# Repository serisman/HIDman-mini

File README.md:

# HIDman-mini
A USB keyboard/mouse to PS/2 (or AT, Serial) computer adapter.

Based on and compatible with: [HIDman](https://github.com/rasteri/HIDman) by [rasteri](https://github.com/rasteri)
 - In the Makefile, make sure the correct `BOARD_TYPE` is selected and then make sure `OSC_TYPE = OSC_INTERNAL` is enabled and `OSC_TYPE = OSC_EXTERNAL` is disabled.  Re-compile and flash the firmware following the instructions found in the HIDman firmware.
   - For HIDman-mini: Choose `BOARD_TYPE = BOARD_AXP` (for ps/2 and serial support), or `BOARD_TYPE = BOARD_MINI` (for just ps/2 support).
   - For HIDman-micro: Choose `BOARD_TYPE = BOARD_MICRO` (only has ps/2 support).
     - Optionally switch to `BOARD_OPTIONS = OPT_SWAP_KBD_MSC` to make it a bit easier to wire up a combo ps/2 port.

### PCBs
- [HIDman-mini](KiCad%20PCBs/HIDman-mini/)
- [HIDman-micro](KiCad%20PCBs/HIDman-micro/)
- [DB9-to-TTL](KiCad%20PCBs/DB9-to-TTL/)

### 3D Printer Models
- [Cover for HIDman-mini](3D%20Printer%20Models/HIDman-mini/)
- [Shell for DB9-to-TTL](3D%20Printer%20Models/DB9-Shell/)

### Schematics
(for HIDman-mini)

(for DB9-to-TTL)

NOTE: Remember to cross-over TxD <--> RxD, and RTS <--> CTS when connecting the two PCBs!

### Optional Configuration: Combo PS/2 Keyboard/Mouse Connector
(for computers that support it)

### Copyright and License:
- Copyright (C) 2022 - serisman (github@serisman.com)
- License: [GPL v3 (or later)](LICENSE)

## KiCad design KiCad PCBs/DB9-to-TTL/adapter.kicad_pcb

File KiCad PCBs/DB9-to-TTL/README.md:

[Home](/README.md)
# PCB: DB9-to-TTL

Order from [OSHPARK](https://oshpark.com/shared_projects/djSCnWyn) or upload [gerber.zip](output/gerber.zip) to your favorite PCB board fabricator.

### Notes:
- Remember to cross-over TxD <--> RxD, and RTS <--> CTS when connecting to the main PCB!
- The older MAX232 can be used in place of the MAX3232.  Might need to change the capacitor values.

### Schematic
- Capacitors are 0603

### Soldered PCB

### Raw PCB

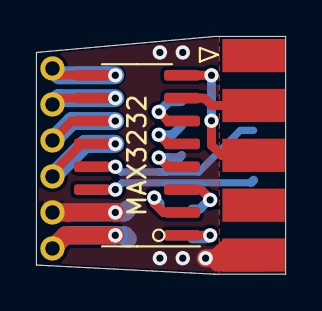
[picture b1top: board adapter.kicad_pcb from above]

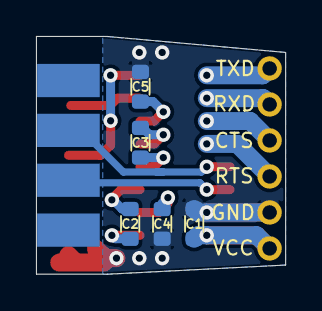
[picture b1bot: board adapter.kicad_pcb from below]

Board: 2 copper layers, 13.8 x 13.2 mm, 8 parts (6 on the bottom side), 16 nets.

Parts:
C1, C2: 100n; C_0603
C3, C4, C5: 1u; C_0603
J1: Conn_01x06; PinHeader_1x06_P2.00mm_Vertical
P1: DB9_Female; DSUB-9_Female_EdgeMount_P2.77mm
U1: MAX3232; SOP-16_3.9x9.9mm_P1.27mm

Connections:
/CTS_232: P1.8, U1.14
/RTS_232: P1.7, U1.13
/RXD_232: P1.2, U1.7
/TXD_232: P1.3, U1.8
CTS: J1.3, U1.11
GND: C1.2, C4.1, C5.1, J1.5, P1.5, U1.15
unnamed: C2.1, U1.1
unnamed: C2.2, U1.3
unnamed: C3.1, U1.4
unnamed: C3.2, U1.5
unnamed: C4.2, U1.2
unnamed: C5.2, U1.6
RTS: J1.4, U1.12
RXD: J1.2, U1.10
TXD: J1.1, U1.9
VCC: C1.1, J1.6, U1.16

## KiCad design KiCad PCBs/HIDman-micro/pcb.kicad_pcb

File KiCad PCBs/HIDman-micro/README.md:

[Home](/README.md)
# PCB: HIDman-micro

Order from [OSHPARK](https://oshpark.com/shared_projects/RKMXx0oz) or upload [gerber.zip](output/gerber.zip) to your favorite PCB board fabricator.

### Notes:
- **WARNING!** Make sure you install the USB port in the correct orientation!
- **WARNING!** Double and Triple check your PS/2 cable pinout to make sure you don't feed 5V where it shouldn't go!

### Firmware

Compatible with HIDman firmware: https://github.com/rasteri/HIDman

```
make clean
make BOARD_TYPE=HIDMAN_MICRO OSC_TYPE=OSC_INTERNAL flash
... or (if you want to swap Keyboard-Data with Mouse-Clock for easier soldering of combo PS/2 port) ...
make clean
make BOARD_TYPE=HIDMAN_MICRO BOARD_OPTIONS=OPT_SWAP_KBD_MSC OSC_TYPE=OSC_INTERNAL flash
```

### Schematic
- USB port P1 (on bottom side) is required for loading code, and can be used for USB keyboard/mouse (including keyboard/mouse combo wireless adapters).
- Hold down SW1 while plugging USB port into computer to force bootloader.
- Resistors are 0603
- Capacitors are 0603 (100n and 3u3) and 0805 (10u)

**WARNING!** This uses a different pinout than HIDman-mini.  Runtime detection can read P4.7, check if it is LOW or floating, and adjust the PS/2 pins accordingly.

### Soldered PCB

### 3D Render

### Raw PCB

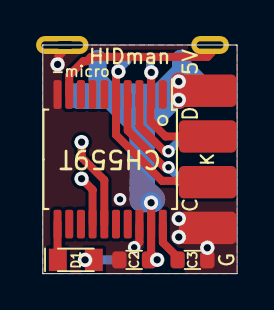
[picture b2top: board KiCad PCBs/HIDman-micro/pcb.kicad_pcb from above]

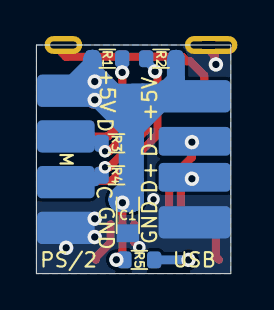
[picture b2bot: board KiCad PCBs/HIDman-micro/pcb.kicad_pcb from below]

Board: 2 copper layers, 10.8 x 12.7 mm, 13 parts (6 on the bottom side), 12 nets.

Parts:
C1: 10u; C_0805
C2: 100n; C_0603
C3: 3u3; C_0603
D1: LED; LED_0805
J1: Conn_02x04_Odd_Even; PinHeader_2x04_P2.54mm_Edge
P1: USB_A; USB_A_Female_SMD_Edge
R1, R2, R3, R4: 2k2; R_0603
R5: 1k; R_0603
SW1: SW_Push; SW_SPST_Edge
U1: CH559T; SSOP-20_5.3x7.2mm_P0.65mm

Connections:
+3V3: C3.1, U1.20
+5V: C1.1, C2.1, J1.1, J1.2, P1.1, R1.1, R2.1, R3.1, R4.1, R5.1, U1.19
GND: C1.2, C2.2, C3.2, J1.7, J1.8, P1.4, SW1.1, U1.10, U1.18
KB_CLK: J1.5, R2.2, U1.5
KB_DATA: J1.3, R1.2, U1.2
MS_CLK: J1.6, R4.2, U1.4
MS_DATA: J1.4, R3.2, U1.3
unnamed: D1.1, U1.11
unnamed: D1.2, R5.2
unnamed: SW1.2, U1.9
USB_D+: P1.3, U1.14
USB_D-: P1.2, U1.15

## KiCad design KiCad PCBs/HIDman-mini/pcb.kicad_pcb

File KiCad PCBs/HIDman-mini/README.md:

[Home](/README.md)
# PCB: HIDman-mini

Order from [OSHPARK](https://oshpark.com/shared_projects/GPxhWAbz) or upload [gerber.zip](output/gerber.zip) to your favorite PCB board fabricator.

### Notes:
- **WARNING!** Make sure you install the CH559 IC in the correct orientation!  There are three dots, making it confusing at a glance (as me how I know!)
- **WARNING!** Make sure you install the USB port(s) in the correct orientation!
- **WARNING!** Double and Triple check your PS/2 cable pinout to make sure you don't feed 5V where it shouldn't go!

### Schematic
- USB port P1 (on bottom side) is required for loading code, and can be used for USB keyboard/mouse (including keyboard/mouse combo wireless adapters).  It can be installed in the middle of the PCB if USB port P2 is not installed.
- USB port P2 (on top side) is optional, but can be installed if a 2nd USB port is needed.  If installed, USB port P1 will have to be lowered a bit.
- Hold down SW1 while plugging USB port P1 into computer to force bootloader.
- Extra-A and Extra-B are not used for anything (yet).  Therefore R5,R6,R11,R12 are not needed.
- R1,R2,R7,R8 are probably not needed.
- Resistors are 0603
- Capacitors are 0603 (100n) and 0805 (3u3+)
- RN1/RN2 are not actually resistor networks.  They are providing the top/bottom solder pads.
- RN3 is 1k (or whatever works with choosen RGB LED)

### Soldered PCB

### Raw PCB

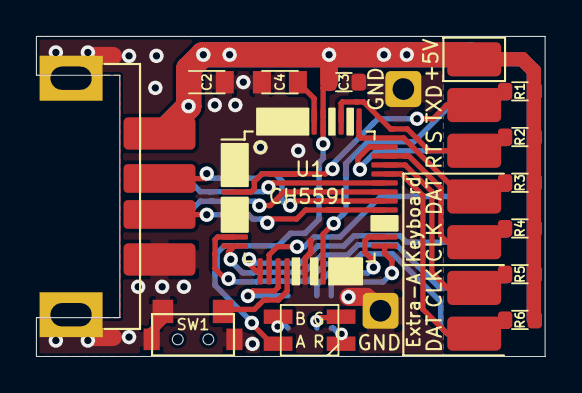
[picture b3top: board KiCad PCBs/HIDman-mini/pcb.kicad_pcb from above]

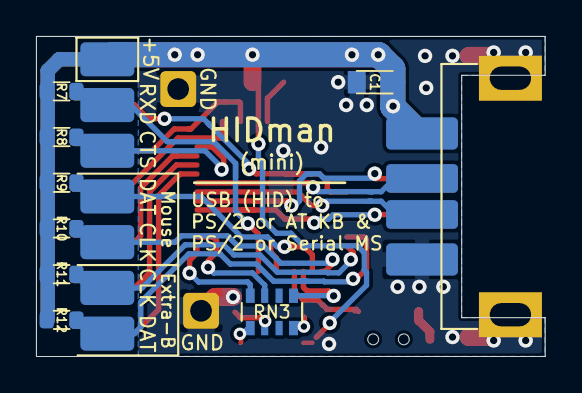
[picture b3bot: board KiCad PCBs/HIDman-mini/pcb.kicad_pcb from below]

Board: 2 copper layers, 28.3 x 17.8 mm, 26 parts (9 on the bottom side), 26 nets.

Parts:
C1, C2, C4: 3u3; C_0805
C3: 100n; C_0603
D1: LED_BAGR; LED_BAGR_3528
J1, J2: Conn_01x01; PinHeader_1x01_P2.54mm_Vertical
P1: USB_A; USB_A_Female_SMD_Edge
P2: USB_A; USB_A_Female_SMD_Top
R1, R2, R3, R4, R5, R6, R7, R8, R9, R10, R11, R12: 10k; R_0603
RN1, RN2: R_Network06; R_Array_SIP7_Edge
RN3: R_Pack04; R_Array_Convex_4x0603
SW1: SW_Push; SW_Push_3.5x4.55_Side
U1: CH559L; LQFP-48_7x7mm_P0.5mm

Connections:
+3V3: C4.1, U1.42
+5V: C1.1, C2.1, C3.1, D1.2, P1.1, P2.1, R1.1, R2.1, R3.1, R4.1, R5.1, R6.1, R7.1, R8.1, R9.1, R10.1, R11.1, R12.1, RN1.1, RN2.1, U1.41
CTS: R8.2, RN2.3, U1.36
GND: C1.2, C2.2, C3.2, C4.2, J1.1, J2.1, P1.4, P2.4, P2.5, SW1.2, U1.18
KB_CLK: R4.2, RN1.5, U1.35
KB_CLK2: R5.2, RN1.6, U1.34
KB_DATA: R3.2, RN1.4, U1.37
KB_DATA2: R6.2, RN1.7, U1.33
MS_CLK: R10.2, RN2.5, U1.13
MS_CLK2: R11.2, RN2.6, U1.12
MS_DATA: R9.2, RN2.4, U1.14
MS_DATA2: R12.2, RN2.7, U1.11
unnamed: D1.1, RN3.4
unnamed: D1.3, RN3.2
unnamed: D1.4, RN3.1
unnamed: P1.2, U1.32
unnamed: P1.3, U1.31
unnamed: P2.2, U1.30
unnamed: P2.3, U1.29
unnamed: RN3.5, U1.15
unnamed: RN3.7, U1.26
unnamed: RN3.8, U1.25
unnamed: SW1.1, U1.16
RTS: R2.2, RN1.3, U1.39
RXD: R7.2, RN2.2, U1.20
TXD: R1.2, RN1.2, U1.6

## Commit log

2022-12-16 Add KiCad PCBs and 3D Printer Models
2022-12-16 Add some pictures
2022-12-16 README.md
2022-12-16 add Gerber files
2022-12-16 Add more README.md files
2022-12-16 Add Home links
2022-12-16 Fix Home links
2022-12-16 Add OSHPARK links
2022-12-16 Attribution
2022-12-16 Add links to 3D files
2022-12-23 Add pictures for Combo PS/2 Keyboard/Mouse option
2022-12-24 Add HIDman-micro. An even smaller version, using CH559T.
2022-12-26 Tweak pad/track size/spacing
2023-01-21 Add some picture of the HIDman-micro
2023-01-21 Move pictures into sub-folders
2023-01-21 Add note about pull request
2023-01-21 Move note
2023-01-27 More verbose DB9-TTL Schematic
2023-01-27 Update firmware instructions for HIDman-micro
2024-09-27 Clarify firmware compile options
